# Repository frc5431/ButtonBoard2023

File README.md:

# 5431ButtonBoard
Custom made button board for frc5431

Designed by Cyrus Lauderdale

Supervised by Tauseef Afraz

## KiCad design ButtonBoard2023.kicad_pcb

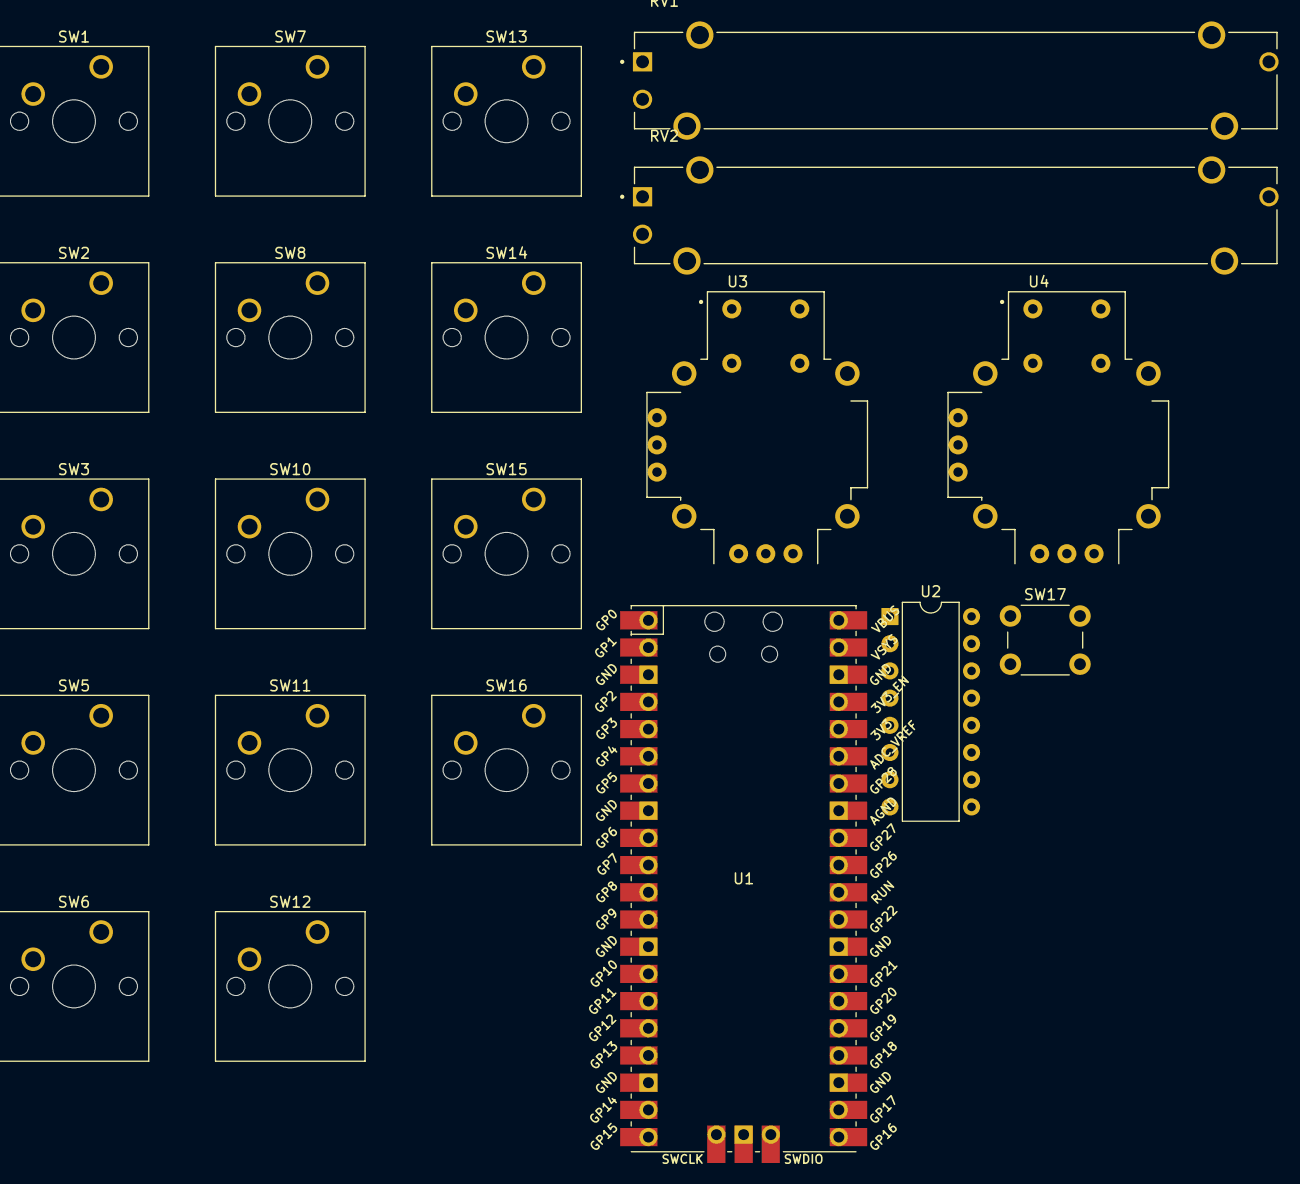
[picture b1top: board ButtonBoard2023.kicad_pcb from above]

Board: 2 copper layers, 21 parts (0 on the bottom side), 31 nets, no tracks yet.

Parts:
RV1, RV2: R_Potentiometer_US; TRIM_PTA4543-2015DPB103
SW1, SW2, SW3, SW5, SW6, SW7, SW8, SW10, SW11, SW12, SW13, SW14, SW15, SW16: SW_DIP_x01; SW_Cherry_MX_1.00u_PCB
SW17: SW_DIP_x01; SW_PUSH_6mm
U1: Pico; RPi_Pico_SMD_TH
U2: MCP3008; DIP-16_W7.62mm
U3, U4: COM-09032; XDCR_COM-09032

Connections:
+3V3: RV1.1, RV2.1, U1.36 (3V3), U2.15 (Vref), U2.16 (Vdd), U3.H1 (H+), U3.V1 (V+), U4.H1 (H+), U4.V1 (V+)
CLK: U1.24 (GPIO18), U2.13 (CLK)
CS: U1.27 (GPIO21), U2.10 (~CS/SHDN)
Din: U1.26 (GPIO20), U2.11 (Din)
Dout: U1.25 (GPIO19), U2.12 (Dout)
GND: RV1.3, RV2.3, SW1.1, SW2.1, SW3.1, SW5.1, SW6.1, SW7.1, SW8.1, SW10.1, SW11.1, SW12.1, SW13.1, SW14.1, SW15.1, SW16.1, SW17.1, U1.3 (GND), U1.8 (GND), U1.13 (GND), U1.18 (GND), U1.23 (GND), U1.28 (GND), U1.38 (GND), U1.42 (GND), U2.9 (DGND), U2.14 (AGND), U3.B2A (SEL-), U3.H3 (H-), U3.V3 (V-), U4.B2A (SEL-), U4.H3 (H-), U4.V3 (V-)
unnamed: RV1.2, U2.1 (CH0)
unnamed: RV2.2, U2.2 (CH1)
unnamed: U3.S1 (SHIELD), U3.S2 (SHIELD), U3.S3 (SHIELD), U3.S4 (SHIELD)
unnamed: U4.S1 (SHIELD), U4.S2 (SHIELD), U4.S3 (SHIELD), U4.S4 (SHIELD)
Reset: SW17.2, U1.30 (RUN)
Sw1: SW1.2, U1.1 (GPIO0)
Sw2: SW2.2, U1.2 (GPIO1)
Sw3: SW3.2, U1.4 (GPIO2)
Sw4: U1.5 (GPIO3), U4.B1A (SEL+)
Sw5: SW5.2, U1.6 (GPIO4)
Sw6: SW6.2, U1.7 (GPIO5)
Sw7: SW7.2, U1.9 (GPIO6)
Sw8: SW8.2, U1.10 (GPIO7)
Sw9: U1.22 (GPIO17), U3.B1A (SEL+)
Sw10: SW10.2, U1.14 (GPIO10)
Sw11: SW11.2, U1.15 (GPIO11)
Sw12: SW12.2, U1.16 (GPIO12)
Sw13: SW13.2, U1.21 (GPIO16)
Sw14: SW14.2, U1.17 (GPIO13)
Sw15: SW15.2, U1.19 (GPIO14)
Sw16: SW16.2, U1.20 (GPIO15)
VRx1: U2.3 (CH2), U3.H2 (H)
VRx2: U2.5 (CH4), U4.H2 (H)
VRy1: U2.4 (CH3), U3.V2 (V)
VRy2: U2.6 (CH5), U4.V2 (V)

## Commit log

2023-03-06 Initial commit. Never again
2023-03-08 initialization
    initialized project
2023-03-13 added schematic libraries
    added libraries
2023-03-13 pico change
    changed to pico
2023-03-13 more changes
    yes
2023-03-14 finished footprints
2023-03-14 footprints plus basic pcb setup
    done
2023-03-15 added pico lib to project only
2023-03-15 Updated sch
2023-03-15 updated layout
2023-03-15 added slider
2023-03-15 added IC footprint-ish
2023-03-15 thing
    thing
2023-03-16 done with parts
    all parts added, need to place, define edge, and wire
2023-03-16 linked mux to pico
2023-03-16 better IC footprint
2023-03-22 final layout
    edge cuts and traces left
2023-04-26 quick organization. might have to redo pcb, but we will see
2023-04-26 added the code
2023-04-27 quick file renaming
2023-04-28 Everything is project assets, hopefully
2023-04-30 Replace pico firmware with C++ implementation
2023-04-30 Move gitignore to root of project
2023-04-30 Apply reported fix
2023-04-30 quick gitignore for build
2023-04-30 rename project to buttonboard, ignore built result
2023-04-30 ported footprints into schematic
    will grab design off my laptop and commit it soon
2023-04-30 branding
2023-05-06 Flash Pico LED
2023-05-06 Always send HID report
2023-05-06 Remove unintended change
2023-05-06 Update offset
2023-05-28 Always send HID report (#3)
